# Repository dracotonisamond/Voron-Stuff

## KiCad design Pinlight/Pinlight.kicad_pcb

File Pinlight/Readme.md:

# RGBW Sequins for Toolheads and Things.

5V for data and power

JLCPCB will do assembly, just specify 0.8mm PCB in green.

Use the files in Pinlight_Panel\Pinlight_ASSY for assembly.

Originally designed for Inolux IN-PI33QBT but JLCPCB has SK6812MINIRGBW that will work too.

This is about 40% brightness of an IN-PI33QBT The SK6812MINIRGBW is slightly dimmer.

https://github.com/dracotonisamond/Voron-Stuff/assets/5184392/2f02287d-d047-42c8-9de1-c4c666919cc7

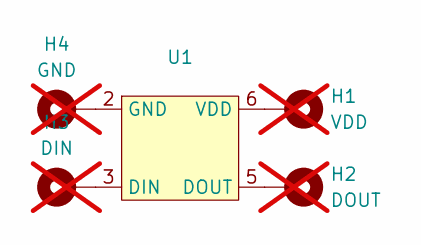
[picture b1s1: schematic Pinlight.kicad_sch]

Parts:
H1: VDD; TestPoint_THTPad_D1.0mm_Drill0.5mm; not fitted
H2: DOUT; TestPoint_THTPad_D1.0mm_Drill0.5mm; not fitted
H3: DIN; TestPoint_THTPad_D1.0mm_Drill0.5mm; not fitted
H4: GND; TestPoint_THTPad_D1.0mm_Drill0.5mm; not fitted
U1: IN_PI33QBTPRPGPBPW_XX; LCSC C7423107

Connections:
unnamed: H1.1, U1.4 (VDD), U1.6 (VDD)
unnamed: H3.1, U1.3 (DIN)
unnamed: H2.1, U1.5 (DOUT)
unnamed: H4.1, U1.2 (GND)

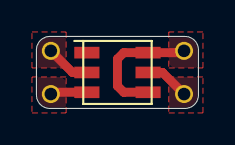
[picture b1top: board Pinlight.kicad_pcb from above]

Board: 2 copper layers, 9.0 x 4.0 mm, 5 parts (0 on the bottom side), 4 nets.

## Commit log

2024-03-12 Add files via upload
    Resolved some weird part positional issues with JLC PCBA format
2024-04-12 Add files via upload
    Fixed Pad issue
2024-04-18 Add files via upload
    Panelization improvements
